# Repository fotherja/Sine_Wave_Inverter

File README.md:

# Sine_Wave_Inverter

This software runs on an atmega328p inside a repurposed inverter. The aim of the project was to have an inverter that could power a mini-fridge inside a campervan from a 24v battery. It draws 250uA when the fridge is off. 

Bought inverters have a quiescent power draw due to the DC/DC converter inside them. Even ~6 Watts = 150wh/day which is horrid when you reliant on solar power. I wanted one that could sense when the fridge is off and enter a low power mode. I also wanted a sine wave output for smooth and efficient running. And hey, why not soft start the fridge to reduce the current stresses at startup?

I bought a £30 2nd hand 24v 300w modified sine wave inverter for it's parts and enclosure. I've tapped off the 320v DC it generates and use this to provide a DC rail for a simple H-Bridge circuit on a custom PCB from OSHpark. The Atmega328p generates the PWM signals to drive this H-Bridge that after filtering form a clean sinewave. 

This software is responsible for generating the PWM. It also enables and disables the inverter's DC-DC (24v-320v) converter which is responsible for most of the quiescent current draw. It monitors the DC input current measured by the ACS712 hall effect sensor to know whether the inverter is powering anything or not and enter a low power mode accordingly. Voltage sensing prevents overdischarge of the battery.

Pin descriptions are clearly defined in the software.

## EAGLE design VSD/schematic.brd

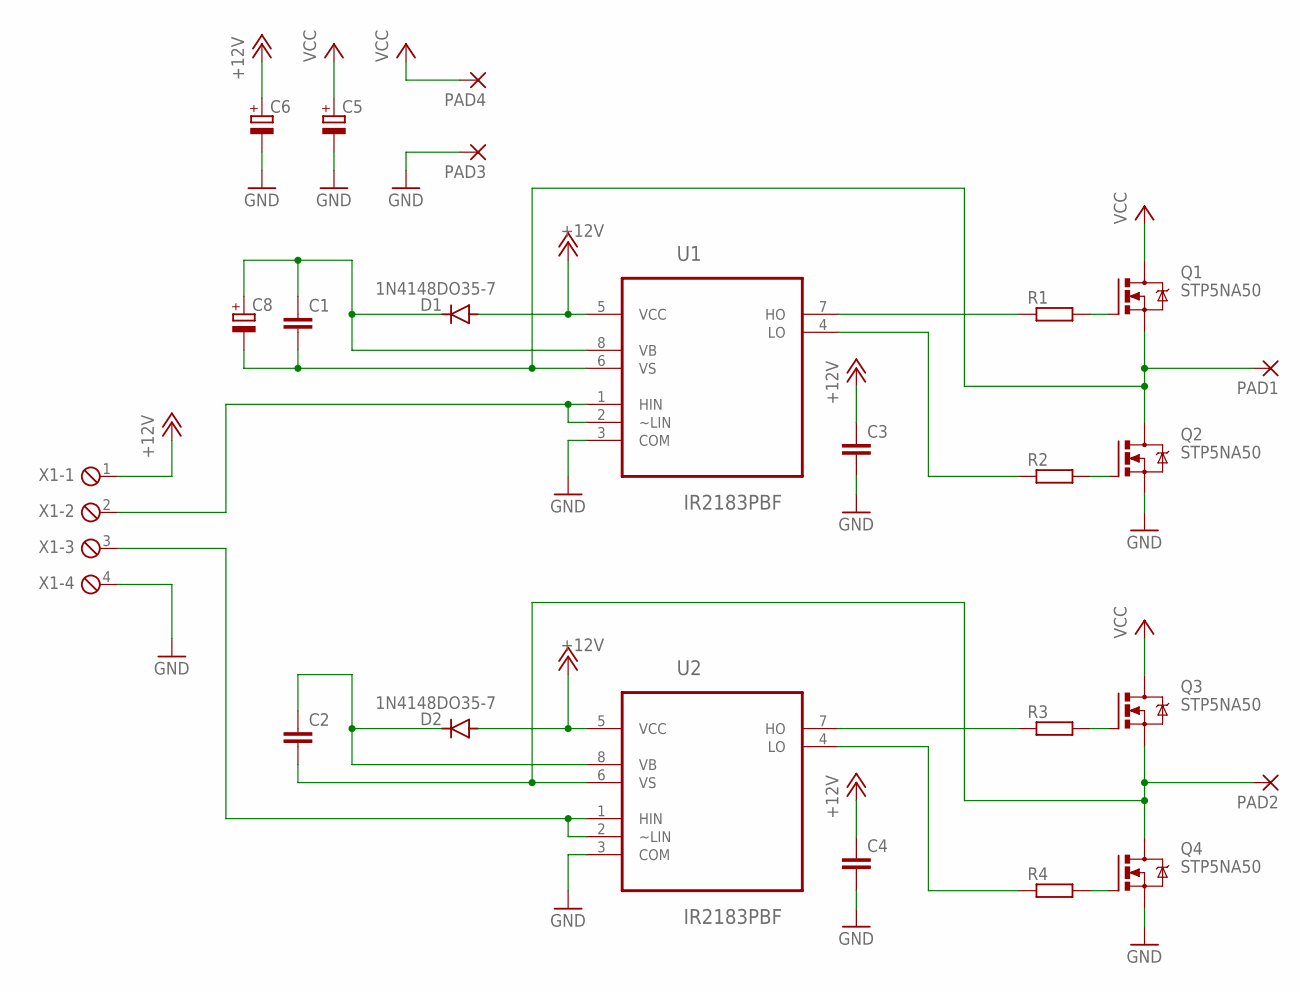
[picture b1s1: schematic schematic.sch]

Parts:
C1, C2, C3, C4: C-EU050-024X044; C050-024X044
C5: CPOL-EUE5-10.5; E5-10,5
C6, C8: CPOL-EUE2.5-6; E2,5-6
D1, D2: 1N4148DO35-7; DO35-7
PAD1, PAD2, PAD3, PAD4: 3,81/1,4
Q1, Q2, Q3, Q4: STP5NA50; TO220BV
R1, R2, R3, R4: R-EU_0204/7; 0204/7
U1, U2: IR2183PBF; DIP254P762X533-8
X1: MPT4; 4POL254

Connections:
+12V: C3.1, C4.1, C6.+, D1.A, D2.A, U1.5 (VCC), U2.5 (VCC), X1.1
GND: C3.2, C4.2, C5.-, C6.-, PAD3.1, Q2.S, Q4.S, U1.3 (COM), U2.3 (COM), X1.4
unnamed: Q2.G, R2.2
unnamed: C1.2, C8.-, PAD1.1, Q1.S, Q2.D, U1.6 (VS)
unnamed: Q1.G, R1.2
unnamed: R1.1, U1.7 (HO)
unnamed: R2.1, U1.4 (LO)
unnamed: C1.1, C8.+, D1.C, U1.8 (VB)
unnamed: U1.1 (HIN), U1.2 (~LIN), X1.2
unnamed: Q4.G, R4.2
unnamed: C2.2, PAD2.1, Q3.S, Q4.D, U2.6 (VS)
unnamed: Q3.G, R3.2
unnamed: R3.1, U2.7 (HO)
unnamed: R4.1, U2.4 (LO)
unnamed: C2.1, D2.C, U2.8 (VB)
unnamed: U2.1 (HIN), U2.2 (~LIN), X1.3
VCC: C5.+, PAD4.1, Q1.D, Q3.D

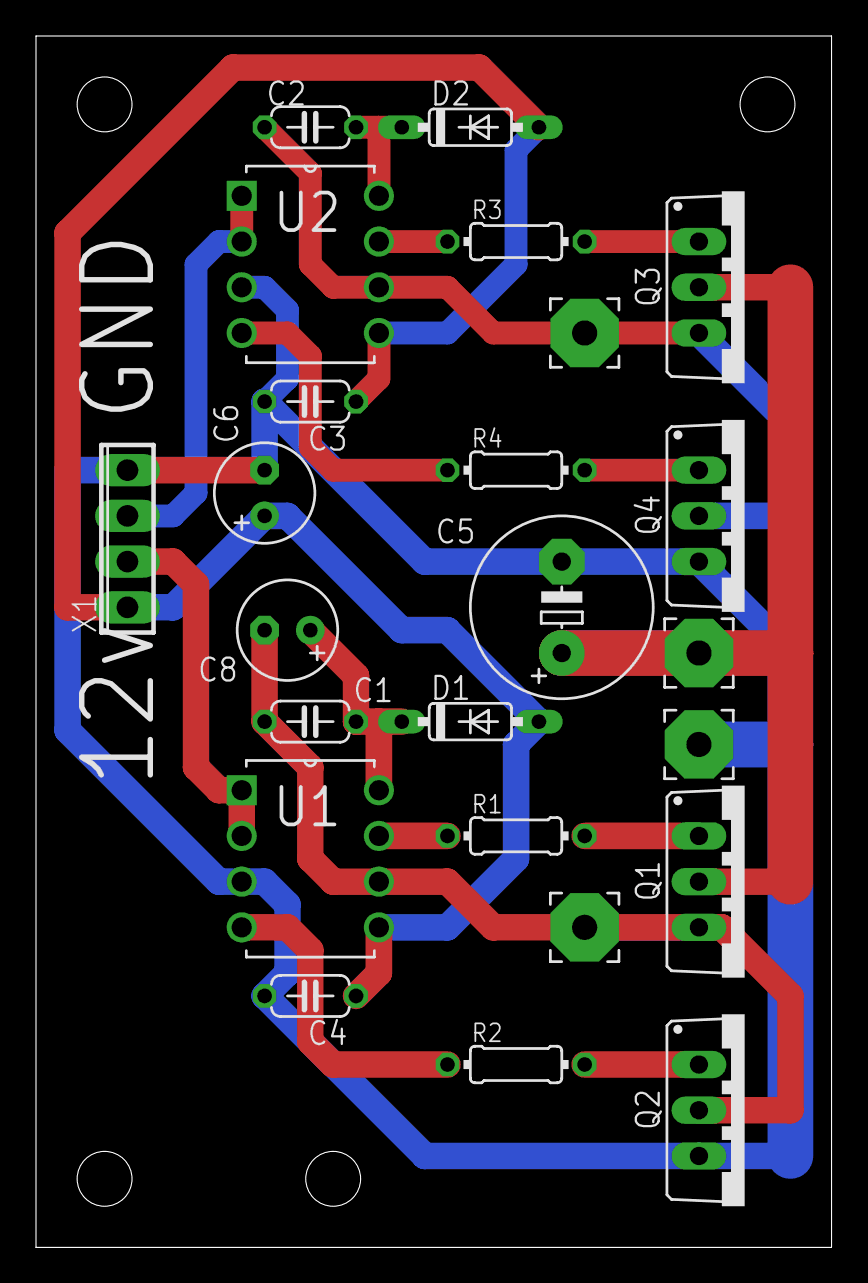
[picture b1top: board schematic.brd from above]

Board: 2 copper layers, 44.2 x 67.3 mm, 24 parts (0 on the bottom side), 17 nets.

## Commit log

2020-01-09 Initial upload
    Bugs:
    - Glitches in waveform
    - ADC slow and no interrupts yet.
2020-01-12 Amplitude changes with Freq
    Further testing. Eventually have one ADC channel measuring the thermistor and the other measuring the input voltage
2020-03-24 Soft_start working
    Yet to do
    - Voltage compensation
    - Load detection and power down
2020-03-25 Thermistor_Controlled_Full
    Full code for thermistor temperature controlled fridge.
    - Needs full hardware testing for temperature hold and voltage cutout/cutin etc
2020-04-26 Uses ACS712 current sensor
    A good solution. Uses the ACS712 on the 24v input to work out whether a load is connected or not by sensing the current draw on power up. If the fridge switches off this is also detected.
    Logic as follows:
    1) Do nothing for 5 minute after turn on -> to allow compressor pressures to equalise (should device be turned off and then straight on again)
    2) Enable the inverter and pause for 2 seconds (Allows the initial inrush current to die down)
    3) Generate a 30Hz output signal
    4) Measure the 24v input current over the next 1 second (Using the ADS712-5A current sensor)
2020-05-17 Fully_working_and_tested
2020-06-22 Detect ACS712 & limit to 45Hz if low input voltage
    If ACS712 not detected, runs as a normal sine wave inverter (with an initial soft start)
    Detects voltage just before startup. If low limit our max frequency to 45Hz to comply with correct volts/Hz
2020-06-22 Added Eagle files for the high voltage H-Bridge
    I built the arduino board housing the voltage regulator, XO, transistor switch to turn the inverter on/off and ADC for input voltage on breadboard. Wish I hadn't.
